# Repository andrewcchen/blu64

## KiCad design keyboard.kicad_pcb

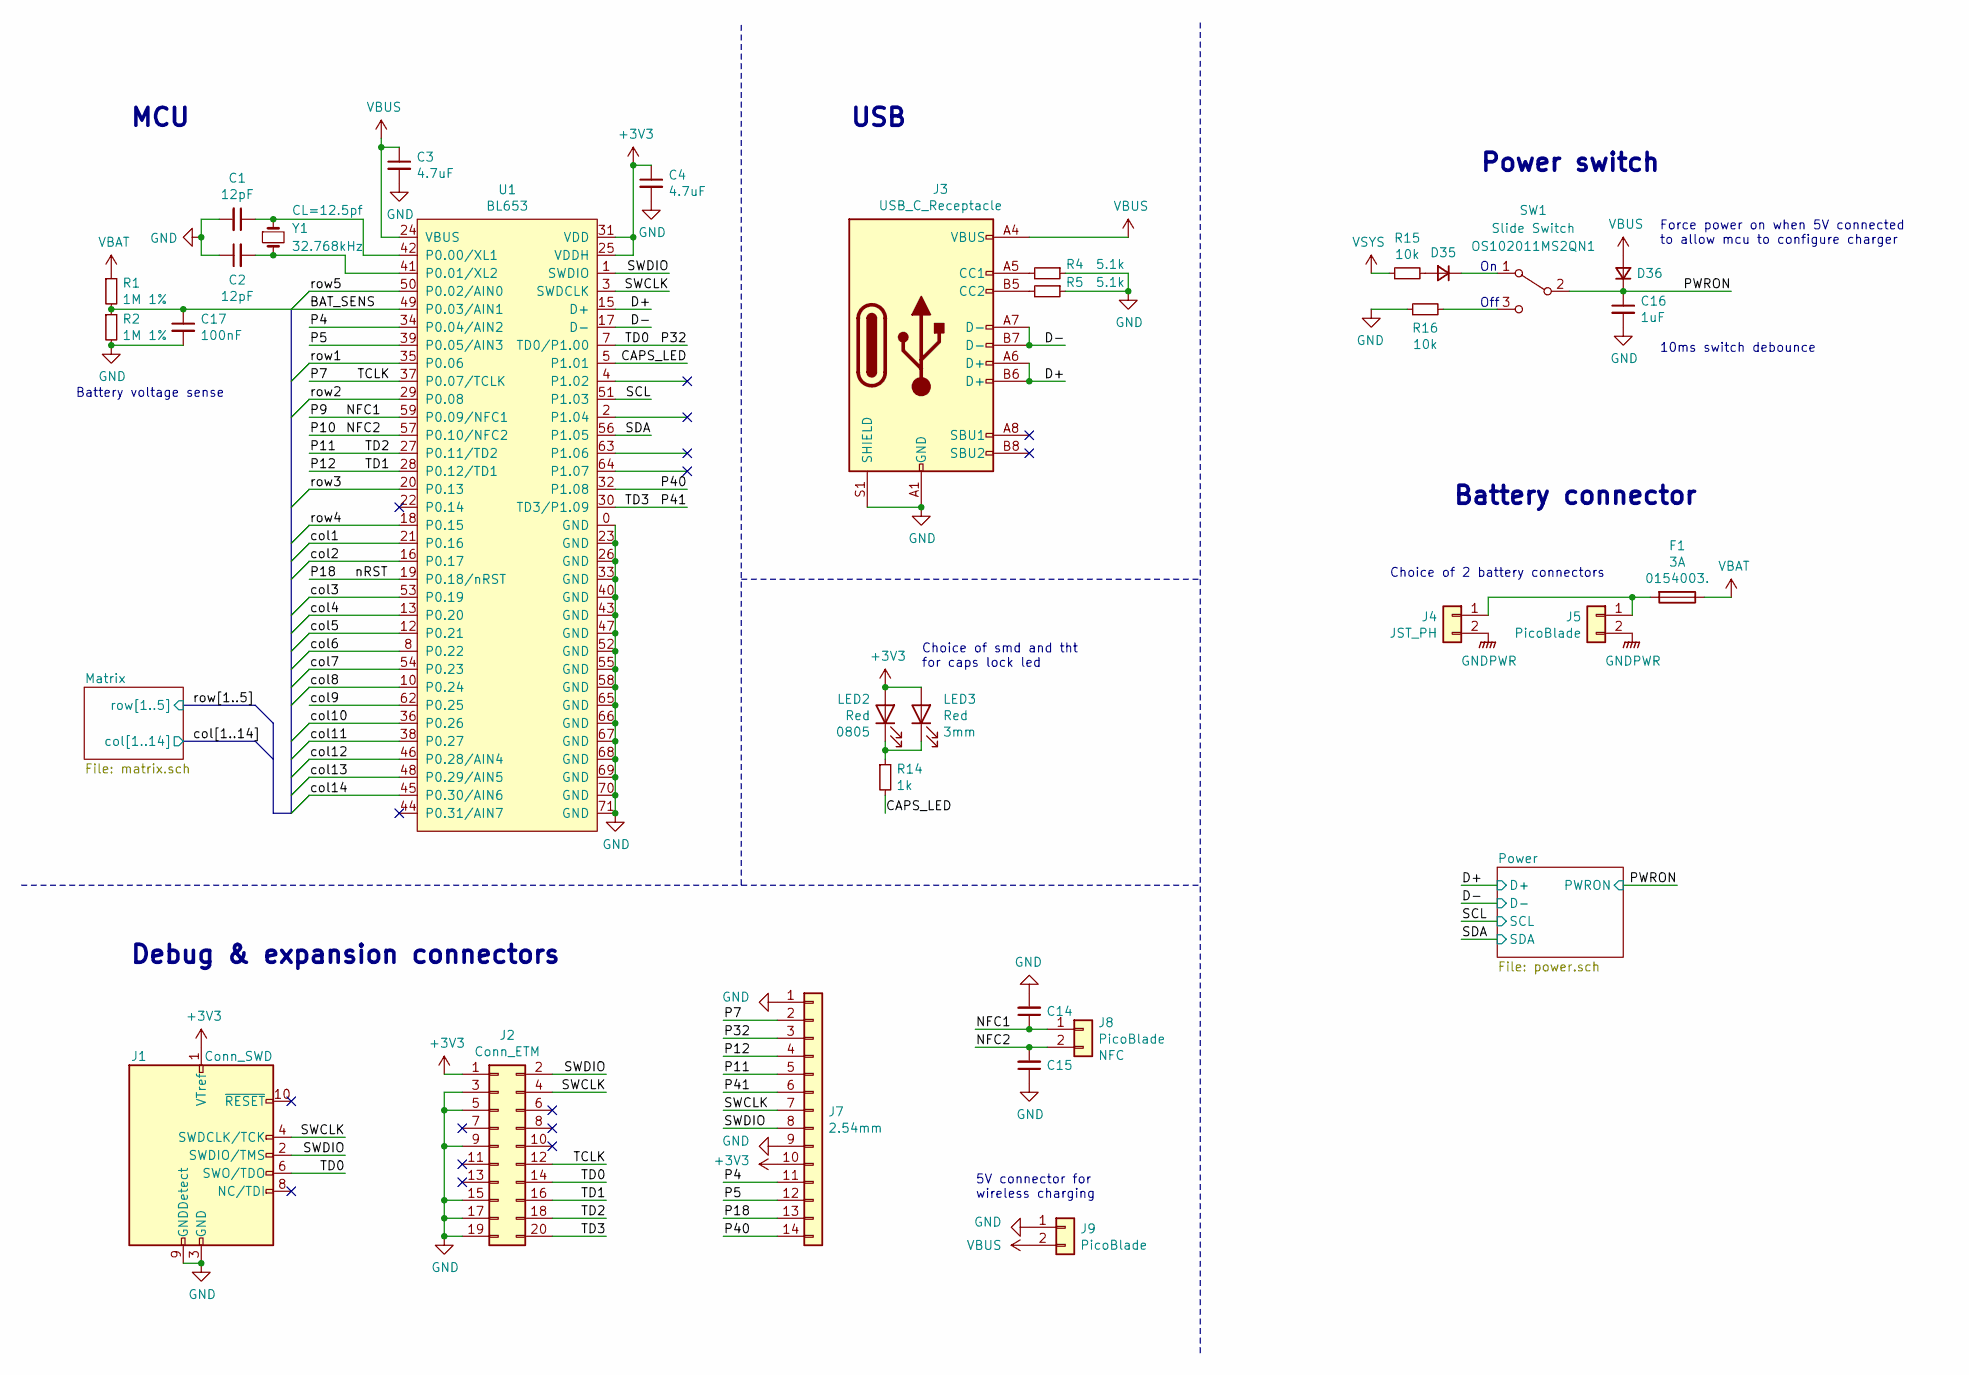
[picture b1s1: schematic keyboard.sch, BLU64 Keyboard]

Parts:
C1, C2: 12pF; C_0805_2012Metric
C3, C4: 4.7uF; C_0805_2012Metric
C14, C15: Ctune; C_0805_2012Metric
C16: 1uF; C_0805_2012Metric
C17: 100nF; C_0805_2012Metric
D35, D36: 1N4007; D_SOD-123; Part SOD-123 1N4007
F1: 3A; Fuseholder_Littelfuse_Nano2_154x; Part 0154003.
J1: Conn_SWD; PinHeader_2x05_P1.27mm_Vertical_SMD; Part FTSH-105-01-L-DV-K
J2: Conn_ETM; PinHeader_2x10_P1.27mm_Vertical_SMD; Part FTSH-110-01-L-DV-K
J3: USB_C_Receptacle; USB_C_Receptacle_HRO_TYPE-C-31-M-12; Part TYPE-C-31-M-12
J4: JST_PH; JST_PH_S2B-PH-SM4-TB_1x02-1MP_P2.00mm_Horizontal; Part S2B-PH-SM4-TB
J5, J8, J9: PicoBlade; Molex_PicoBlade_53261-0271_1x02-1MP_P1.25mm_Horizontal; Part 53261-0271
J7: 2.54mm; PinHeader_1x14_P2.54mm_Vertical
LED2: Red; LED_0805_2012Metric
LED3: Red; LED_D3.0mm
R1, R2: 1M 1%; R_0805_2012Metric
R4, R5: 5.1k; R_0805_2012Metric
R14: 1k; R_0805_2012Metric
R15, R16: 10k; R_0805_2012Metric
SW1: Slide Switch; SW_OS102011MS2QN1; Part OS102011MS2QN1
U1: BL653; Laird_BL653; Part 453-00039
Y1: 32.768kHz; Crystal_SMD_3215-2Pin_3.2x1.5mm

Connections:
+3V3: C4.1, J1.1 (VTref), J2.1, J7.10, LED2.2 (A), LED3.2 (A), U1.25 (VDDH), U1.31 (VDD); also elsewhere on the board
/BAT_SENS: C17.1, R1.2, R2.1, U1.49 (P0.03/AIN1)
/CAPS_LED: R14.2, U1.5 (P1.01)
/D+: J3.A6 (D+), J3.B6 (D+), U1.15 (D+); also elsewhere on the board
/D-: J3.A7 (D-), J3.B7 (D-), U1.17 (D-); also elsewhere on the board
/NFC1: C14.1, J8.1, U1.59 (P0.09/NFC1)
/NFC2: C15.2, J8.2, U1.57 (P0.10/NFC2)
/P4: J7.11, U1.34 (P0.04/AIN2)
/P5: J7.12, U1.39 (P0.05/AIN3)
/P7: J2.12, J7.2, U1.37 (P0.07/TCLK)
/P11: J2.18, J7.5, U1.27 (P0.11/TD2)
/P12: J2.16, J7.4, U1.28 (P0.12/TD1)
/P18: J7.13, U1.19 (P0.18/nRST)
/P32: J1.6 (SWO/TDO), J2.14, J7.3, U1.7 (TD0/P1.00)
/P40: J7.14, U1.32 (P1.08)
/P41: J2.20, J7.6, U1.30 (TD3/P1.09)
/PWRON: C16.1, D36.1 (K), SW1.2 (B); also elsewhere on the board
/SCL: U1.51 (P1.03); also elsewhere on the board
/SDA: U1.56 (P1.05); also elsewhere on the board
/SWCLK: J1.4 (SWDCLK/TCK), J2.4, J7.7, U1.3 (SWDCLK)
/SWDIO: J1.2 (SWDIO/TMS), J2.2, J7.8, U1.1 (SWDIO)
/col1: U1.21 (P0.16); also elsewhere on the board
/col2: U1.16 (P0.17); also elsewhere on the board
/col3: U1.53 (P0.19); also elsewhere on the board
/col4: U1.13 (P0.20); also elsewhere on the board
/col5: U1.12 (P0.21); also elsewhere on the board
/col6: U1.8 (P0.22); also elsewhere on the board
/col7: U1.54 (P0.23); also elsewhere on the board
/col8: U1.10 (P0.24); also elsewhere on the board
/col9: U1.62 (P0.25); also elsewhere on the board
/col10: U1.36 (P0.26); also elsewhere on the board
/col11: U1.38 (P0.27); also elsewhere on the board
/col12: U1.46 (P0.28/AIN4); also elsewhere on the board
/col13: U1.48 (P0.29/AIN5); also elsewhere on the board
/col14: U1.45 (P0.30/AIN6); also elsewhere on the board
/row1: U1.35 (P0.06); also elsewhere on the board
/row2: U1.29 (P0.08); also elsewhere on the board
/row3: U1.20 (P0.13); also elsewhere on the board
/row4: U1.18 (P0.15); also elsewhere on the board
/row5: U1.50 (P0.02/AIN0); also elsewhere on the board
GND: C1.2, C2.1, C3.2, C4.2, C14.2, C15.1, C16.2, C17.2, J1.3 (GND), J1.5 (GND), J1.9 (GNDDetect), J2.3, J2.5, J2.9, J2.15, J2.17, J2.19, J3.A1 (GND), J3.A12 (GND), J3.B1 (GND), J3.B12 (GND), J3.S1 (SHIELD), J7.1, J7.9, J9.1, R2.2, R4.1, R5.1, R16.1, U1.0 (GND), U1.23 (GND), U1.26 (GND), U1.33 (GND), U1.40 (GND), U1.43 (GND), U1.47 (GND), U1.52 (GND), U1.55 (GND), U1.58 (GND), U1.65 (GND), U1.66 (GND), U1.67 (GND), U1.68 (GND), U1.69 (GND), U1.70 (GND), U1.71 (GND); also elsewhere on the board
GNDPWR: J4.2, J5.2; also elsewhere on the board
unnamed: C1.1, U1.42 (P0.00/XL1), Y1.1
unnamed: C2.2, U1.41 (P0.01/XL2), Y1.2
unnamed: D35.1 (K), SW1.1 (A)
unnamed: D35.2 (A), R15.2
unnamed: F1.2, J4.1, J5.1
unnamed: J3.A5 (CC1), R4.2
unnamed: J3.B5 (CC2), R5.2
unnamed: LED2.1 (K), LED3.1 (K), R14.1
unnamed: R16.2, SW1.3 (C)
VBAT: F1.1, R1.1; also elsewhere on the board
VBUS: C3.1, D36.2 (A), J3.A4 (VBUS), J3.A9 (VBUS), J3.B4 (VBUS), J3.B9 (VBUS), J9.2, U1.24 (VBUS); also elsewhere on the board
VSYS: R15.1; also elsewhere on the board

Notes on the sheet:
MCU
Debug & expansion connectors
USB
5V connector for wireless charging
Battery voltage sense
Choice of smd and tht for caps lock led
Force power on when 5V connected to allow mcu to configure charger
10ms switch debounce
Off
Choice of 2 battery connectors
Power switch
Battery connector

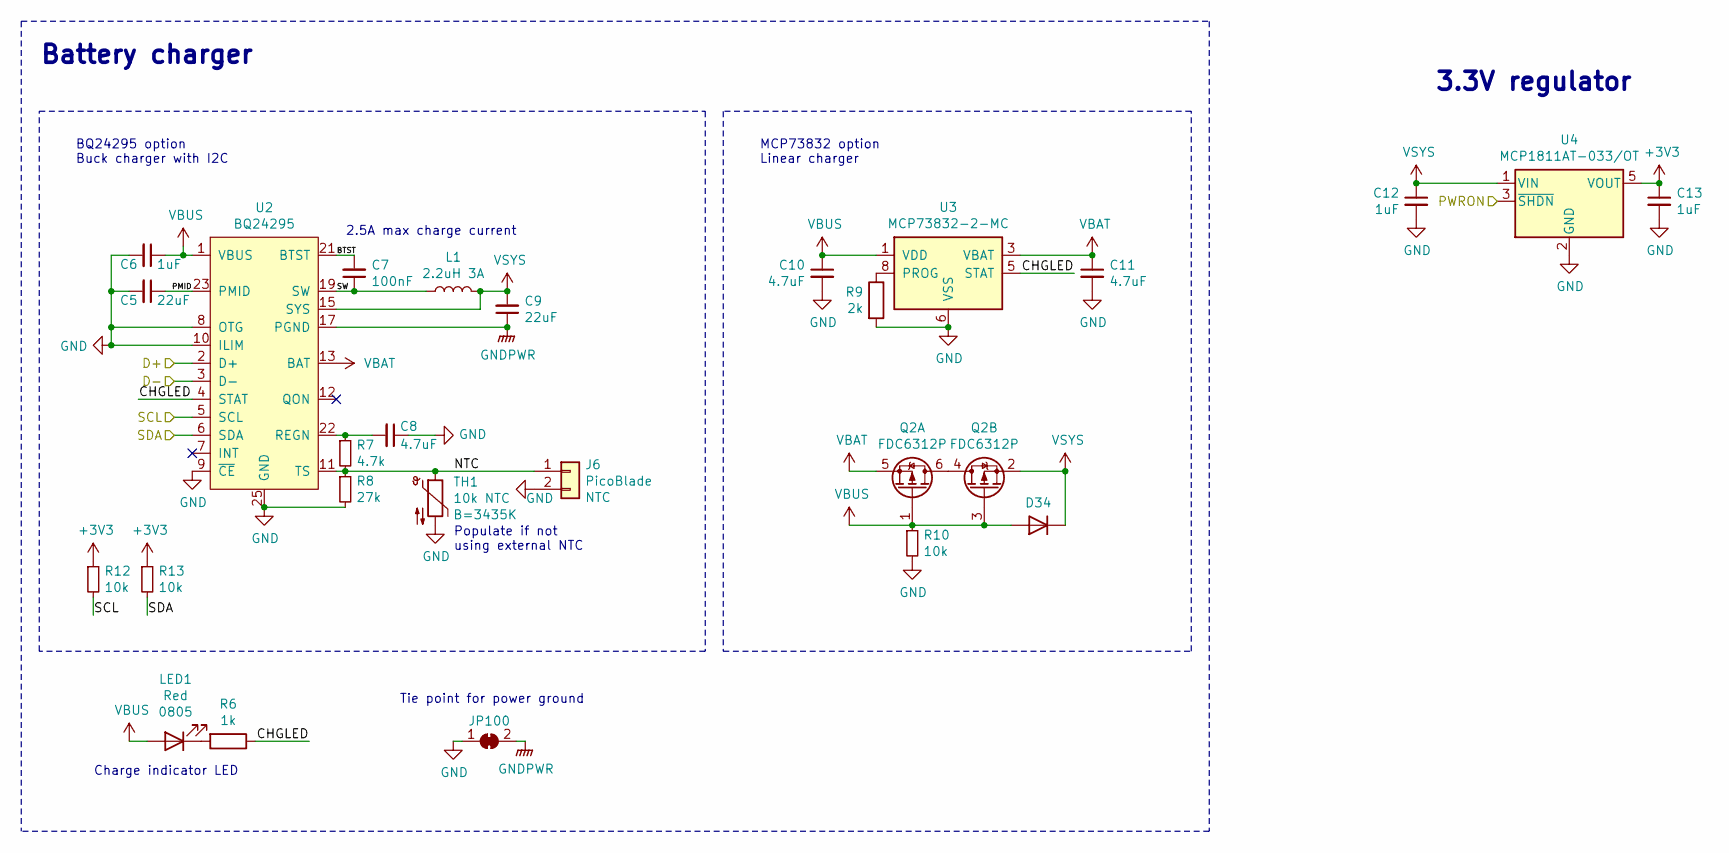
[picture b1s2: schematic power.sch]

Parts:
C5, C12, C13: 1uF; C_0805_2012Metric
C6, C9: 22uF; C_1206_3216Metric
C7: 100nF; C_0805_2012Metric
C8, C10, C11: 4.7uF; C_0805_2012Metric
D34: 1N4007; D_SOD-123; Part SOD-123 1N4007
J6: PicoBlade; Molex_PicoBlade_53261-0271_1x02-1MP_P1.25mm_Horizontal; Part 53261-0271
JP100: Jumper_2_Bridged; GND_Tie
L1: 2.2uH 3A; L_Bourns-SRN4018; Part BCIHP0420TB-2R2M
LED1: Red; LED_0805_2012Metric
Q2: FDC6312P; SuperSOT-6; Part FDC6312P
R6: 1k; R_0805_2012Metric
R7: 4.7k; R_0805_2012Metric
R8: 27k; R_0805_2012Metric
R9: 2k; R_0805_2012Metric
R10, R12, R13: 10k; R_0805_2012Metric
TH1: 10k NTC; R_0805_2012Metric
U2: BQ24295; QFN-24-1EP_4x4mm_P0.5mm_EP2.65x2.65mm; Part BQ24295
U3: MCP73832-2-MC; DFN-8-1EP_3x2mm_P0.5mm_EP1.7x1.4mm; Part MCP73832-2ACI/MC
U4: MCP1811AT-033/OT; SOT-23-5; Part MCP1811AT-033/OT

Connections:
+3V3: C13.1, R12.1, R13.1, U4.5 (VOUT); also elsewhere on the board
/D+: U2.2 (D+); also elsewhere on the board
/D-: U2.3 (D-); also elsewhere on the board
/PWRON: U4.3 (~SHDN); also elsewhere on the board
/Power/BTST: C7.2, U2.21 (BTST)
/Power/CHGLED: R6.1, U2.4 (STAT), U3.5 (STAT)
/Power/NTC: J6.1, R7.2, R8.1, TH1.1, U2.11 (TS)
/Power/PMID: C6.1, U2.23 (PMID)
/Power/SW: C7.1, L1.1, U2.19 (SW), U2.20 (SW)
/SCL: R12.2, U2.5 (SCL); also elsewhere on the board
/SDA: R13.2, U2.6 (SDA); also elsewhere on the board
GND: C5.2, C6.2, C8.1, C10.2, C11.2, C12.2, C13.2, J6.2, JP100.1 (A), R8.2, R9.2, R10.2, TH1.2, U2.8 (OTG), U2.9 (~CE), U2.10 (ILIM), U2.25 (GND), U3.6 (VSS), U3.9 (VSS), U4.2 (GND); also elsewhere on the board
GNDPWR: C9.1, JP100.2 (B), U2.17 (PGND), U2.18 (PGND); also elsewhere on the board
unnamed: C8.2, R7.1, U2.22 (REGN)
unnamed: LED1.1 (K), R6.2
unnamed: Q2.4 (D), Q2.6 (D)
unnamed: R9.1, U3.8 (PROG)
VBAT: C11.1, Q2.5 (S), U2.13 (BAT), U2.14 (BAT), U3.3 (VBAT), U3.4 (VBAT); also elsewhere on the board
VBUS: C5.1, C10.1, D34.2 (A), LED1.2 (A), Q2.1 (G), Q2.3 (G), R10.1, U2.1 (VBUS), U2.24 (VBUS), U3.1 (VDD), U3.2 (VDD); also elsewhere on the board
VSYS: C9.2, C12.1, D34.1 (K), L1.2, Q2.2 (S), U2.15 (SYS), U2.16 (SYS), U4.1 (VIN); also elsewhere on the board

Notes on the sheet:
2.5A max charge current
Populate if not using external NTC
BQ24295 option Buck charger with I2C
MCP73832 option Linear charger
Charge indicator LED
Battery charger
Tie point for power ground
3.3V regulator

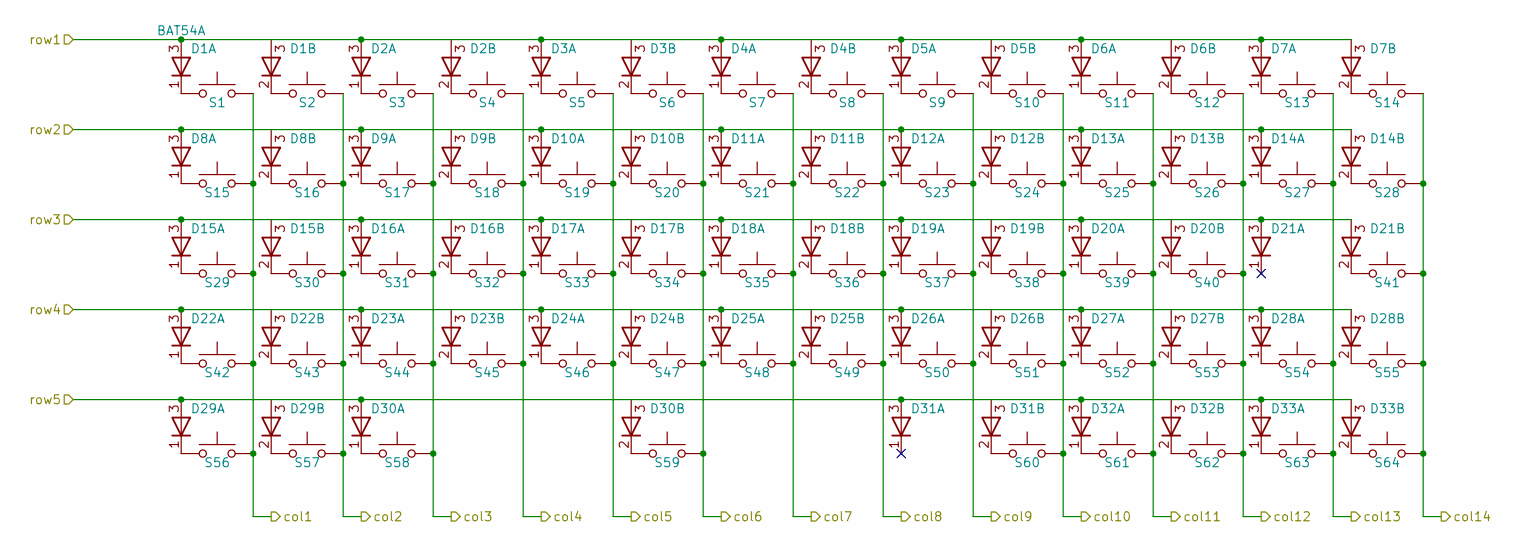
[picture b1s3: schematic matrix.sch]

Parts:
D1, D2, D3, D4, D5, D6, D7, D8, D9, D10, D11, D12, D13, D14, D15, D16, D17, D18, D19, D20, D21, D22, D23, D24, D25, D26, D27, D28, D29, D30, D31, D32, D33: BAT54A; SOT-23; Part BAT54A
S1, S2, S3, S4, S5, S6, S7, S8, S9, S10, S11, S12, S13, S16, S17, S18, S19, S20, S21, S22, S23, S24, S25, S26, S27, S30, S31, S32, S33, S34, S35, S36, S37, S38, S39, S40, S43, S44, S45, S46, S47, S48, S49, S50, S51, S52, S53, S54, S55, S60, S61, S62, S63, S64: MX1A; SW_Cherry_MX_1.00u_PCB
S14, S42: MX1A; SW_Cherry_MX_2.00u_PCB
S15, S28: MX1A; SW_Cherry_MX_1.50u_PCB
S29: MX1A; SW_Cherry_MX_1.75u_PCB
S41: MX1A; SW_Cherry_MX_2.25u_PCB
S56, S57, S58: MX1A; SW_Cherry_MX_1.25u_PCB
S59: MX1A; SW_Cherry_MX_6.25u_PCB

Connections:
/col1: S1.2, S15.2, S29.2, S42.2, S56.2; also elsewhere on the board
/col2: S2.2, S16.2, S30.2, S43.2, S57.2; also elsewhere on the board
/col3: S3.2, S17.2, S31.2, S44.2, S58.2; also elsewhere on the board
/col4: S4.2, S18.2, S32.2, S45.2; also elsewhere on the board
/col5: S5.2, S19.2, S33.2, S46.2; also elsewhere on the board
/col6: S6.2, S20.2, S34.2, S47.2, S59.2; also elsewhere on the board
/col7: S7.2, S21.2, S35.2, S48.2; also elsewhere on the board
/col8: S8.2, S22.2, S36.2, S49.2; also elsewhere on the board
/col9: S9.2, S23.2, S37.2, S50.2; also elsewhere on the board
/col10: S10.2, S24.2, S38.2, S51.2, S60.2; also elsewhere on the board
/col11: S11.2, S25.2, S39.2, S52.2, S61.2; also elsewhere on the board
/col12: S12.2, S26.2, S40.2, S53.2, S62.2; also elsewhere on the board
/col13: S13.2, S27.2, S54.2, S63.2; also elsewhere on the board
/col14: S14.2, S28.2, S41.2, S55.2, S64.2; also elsewhere on the board
/row1: D1.3 (A), D2.3 (A), D3.3 (A), D4.3 (A), D5.3 (A), D6.3 (A), D7.3 (A); also elsewhere on the board
/row2: D8.3 (A), D9.3 (A), D10.3 (A), D11.3 (A), D12.3 (A), D13.3 (A), D14.3 (A); also elsewhere on the board
/row3: D15.3 (A), D16.3 (A), D17.3 (A), D18.3 (A), D19.3 (A), D20.3 (A), D21.3 (A); also elsewhere on the board
/row4: D22.3 (A), D23.3 (A), D24.3 (A), D25.3 (A), D26.3 (A), D27.3 (A), D28.3 (A); also elsewhere on the board
/row5: D29.3 (A), D30.3 (A), D31.3 (A), D32.3 (A), D33.3 (A); also elsewhere on the board
unnamed: D1.1 (K), S1.1
unnamed: D1.2 (K), S2.1
unnamed: D2.1 (K), S3.1
unnamed: D2.2 (K), S4.1
unnamed: D3.1 (K), S5.1
unnamed: D3.2 (K), S6.1
unnamed: D4.1 (K), S7.1
unnamed: D4.2 (K), S8.1
unnamed: D5.1 (K), S9.1
unnamed: D5.2 (K), S10.1
unnamed: D6.1 (K), S11.1
unnamed: D6.2 (K), S12.1
unnamed: D7.1 (K), S13.1
unnamed: D7.2 (K), S14.1
unnamed: D8.1 (K), S15.1
unnamed: D8.2 (K), S16.1
unnamed: D9.1 (K), S17.1
unnamed: D9.2 (K), S18.1
unnamed: D10.1 (K), S19.1
unnamed: D10.2 (K), S20.1
unnamed: D11.1 (K), S21.1
unnamed: D11.2 (K), S22.1
unnamed: D12.1 (K), S23.1
unnamed: D12.2 (K), S24.1
unnamed: D13.1 (K), S25.1
unnamed: D13.2 (K), S26.1
unnamed: D14.1 (K), S27.1
unnamed: D14.2 (K), S28.1
unnamed: D15.1 (K), S29.1
unnamed: D15.2 (K), S30.1
unnamed: D16.1 (K), S31.1
unnamed: D16.2 (K), S32.1
unnamed: D17.1 (K), S33.1
unnamed: D17.2 (K), S34.1
unnamed: D18.1 (K), S35.1
unnamed: D18.2 (K), S36.1
unnamed: D19.1 (K), S37.1
unnamed: D19.2 (K), S38.1
unnamed: D20.1 (K), S39.1
unnamed: D20.2 (K), S40.1
unnamed: D21.2 (K), S41.1
unnamed: D22.1 (K), S42.1
unnamed: D22.2 (K), S43.1
unnamed: D23.1 (K), S44.1
unnamed: D23.2 (K), S45.1
unnamed: D24.1 (K), S46.1
unnamed: D24.2 (K), S47.1
unnamed: D25.1 (K), S48.1
unnamed: D25.2 (K), S49.1
unnamed: D26.1 (K), S50.1
unnamed: D26.2 (K), S51.1
unnamed: D27.1 (K), S52.1
unnamed: D27.2 (K), S53.1
unnamed: D28.1 (K), S54.1
unnamed: D28.2 (K), S55.1
unnamed: D29.1 (K), S56.1
unnamed: D29.2 (K), S57.1
unnamed: D30.1 (K), S58.1
unnamed: D30.2 (K), S59.1
unnamed: D31.2 (K), S60.1
unnamed: D32.1 (K), S61.1
unnamed: D32.2 (K), S62.1
unnamed: D33.1 (K), S63.1
unnamed: D33.2 (K), S64.1

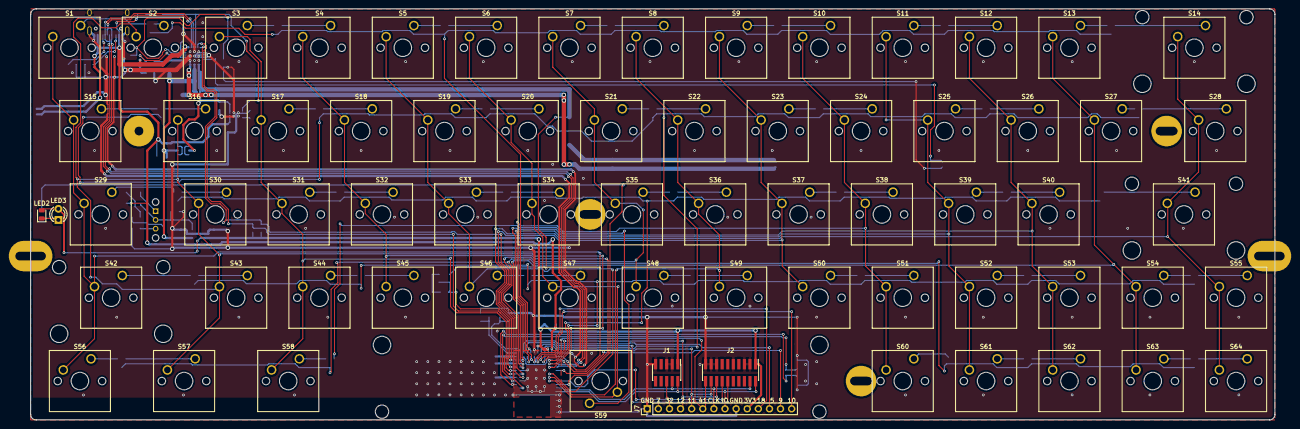
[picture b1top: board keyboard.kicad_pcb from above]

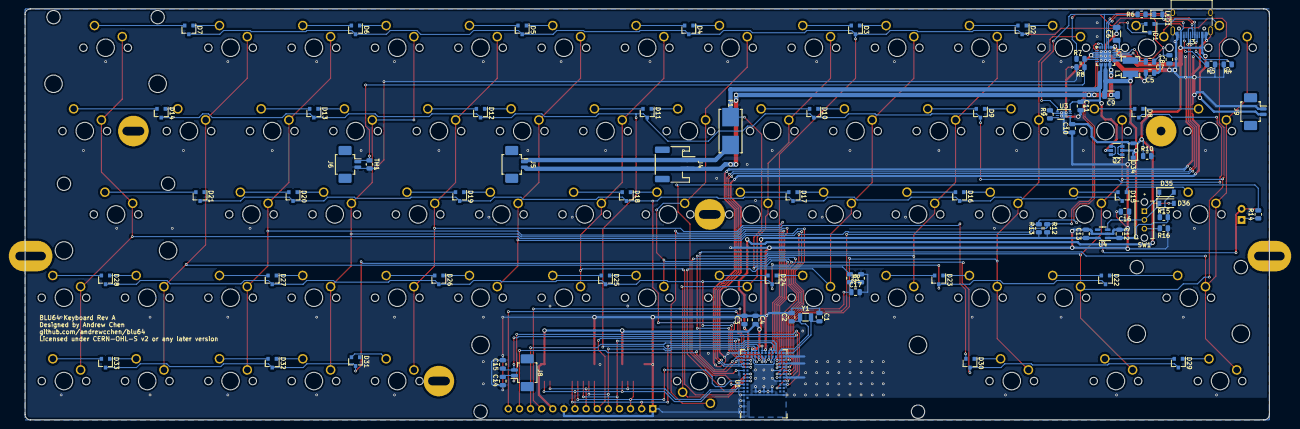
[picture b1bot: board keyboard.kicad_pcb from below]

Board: 2 copper layers, 284.5 x 94.0 mm, 160 parts (85 on the bottom side), 127 nets.

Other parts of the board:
MK1: Hole_1
MK2, MK3, MK6: Hole_2
MK4, MK5: Hole_3

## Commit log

2021-02-02 initial import
2021-02-03 power routed
2021-02-03 all routed
2021-02-03 almost ready rev a
2021-02-04 improve power switch circuit
2021-02-04 final changes to power switch circuitry
2021-02-05 Rev A complete
2021-02-14 Change diode part BAS70 -> BAT54
    Use lower voltage diode for better forward voltage
2021-02-23 prettyify schematics a little
2021-02-24 oops switch on wrong side of board
    only affects silkscreen
2021-03-07 Fix battery sense quiescent current draw
    Q1 was useless because current still sinks through the mcu's esd diodes
2021-03-07 update gitignore
2021-03-07 archive footprints and schematics symbols
2021-03-07 small change to expansion header pinout

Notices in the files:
keyboard.kicad_pcb:
Licensed under CERN-OHL-S v2 or any later version
Copyright (c) 2021 Andrew Chen
